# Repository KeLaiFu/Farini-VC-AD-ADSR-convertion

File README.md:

# Farini-VC-AD-ADSR-convertion
An attempt to convert a 3310 based VC ADSR from Kosmo format, to Eurorack

'3320' on the panel has been fixed!

Original Kosmo module by Dave can be found here:
https://github.com/DavesKosmoModules/Farini-VC-ADSR
Cheers Dave!

Current Status : initial build tested with spectacular results! My entire rack stopped producing audio apart from a high pitched noise coming from the PSU, so, I think I'll chalk this one up as a fail. My only 3310 chip is probably toasted now too, so I can't really continue to work on this, sadly.

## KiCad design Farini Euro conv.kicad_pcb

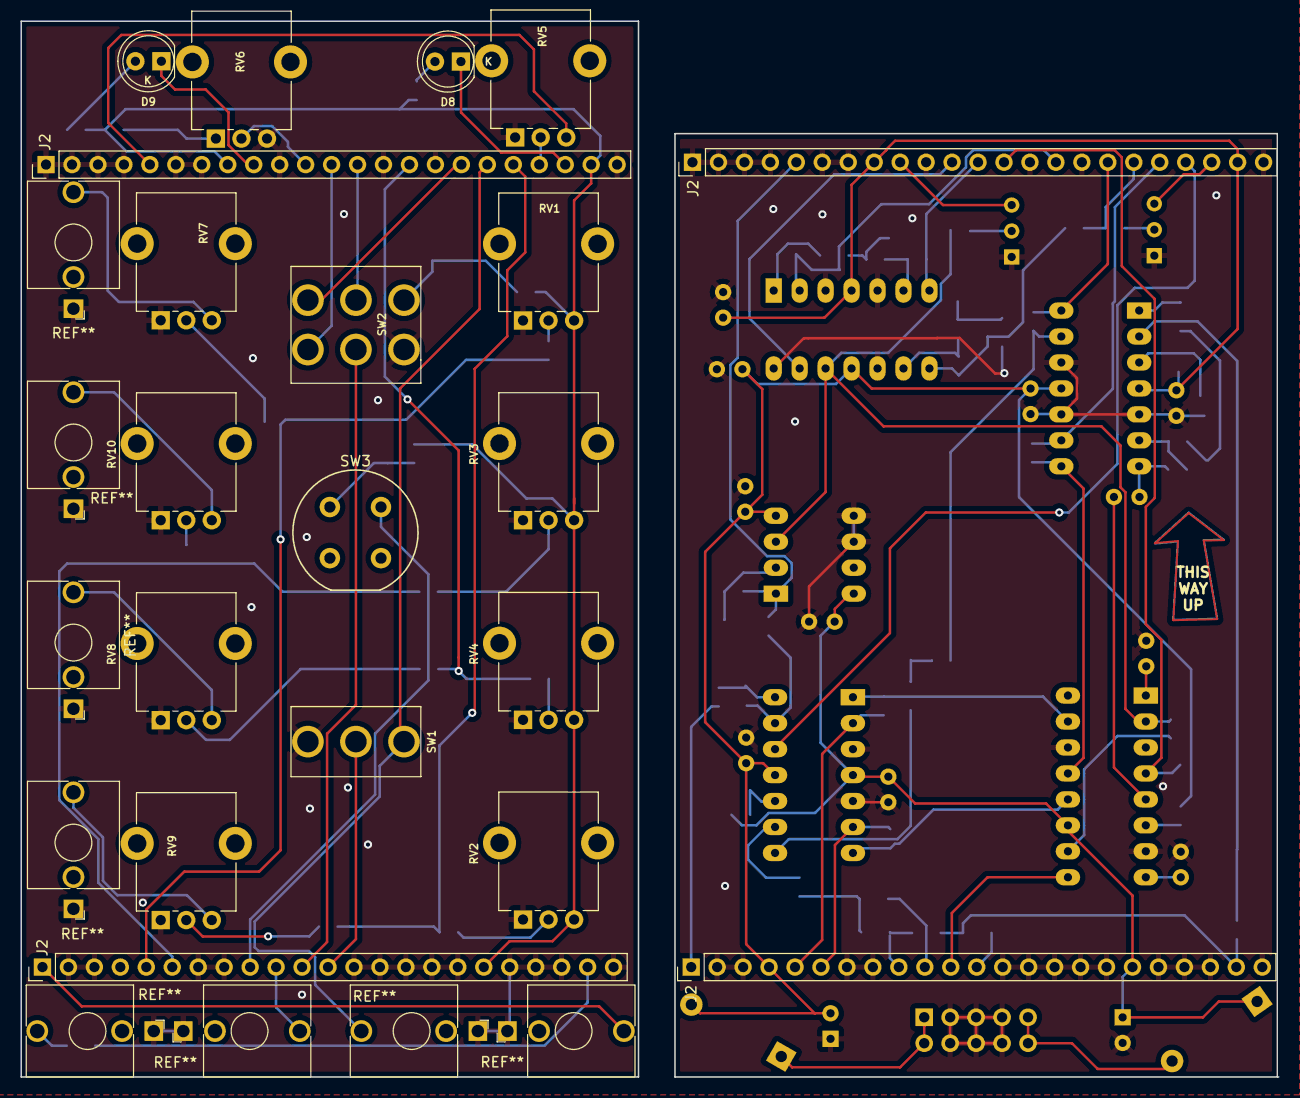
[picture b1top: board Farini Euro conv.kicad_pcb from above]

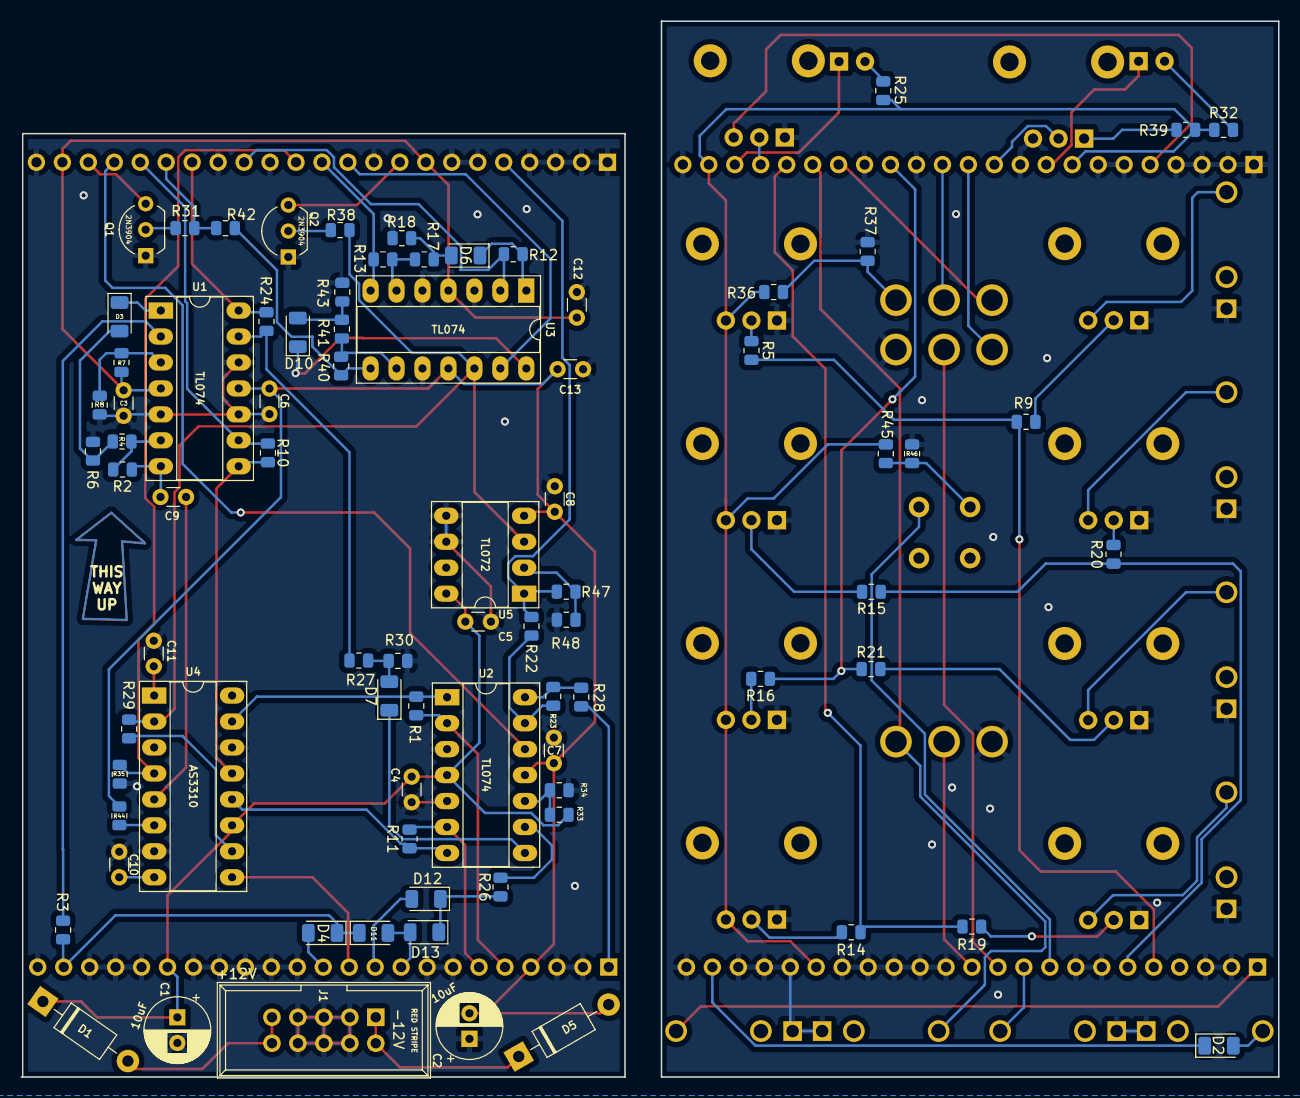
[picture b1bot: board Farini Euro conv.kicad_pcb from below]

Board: 2 copper layers, 123.1 x 103.3 mm, 99 parts (80 on the bottom side), 70 nets.

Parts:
C1, C2: 10uF; CP_Radial_D6.3mm_P2.50mm
C3, C4, C5, C6, C7, C8, C12, C13: 0.1uF; C_Disc_D3.0mm_W1.6mm_P2.50mm
C9: 0.001uF; C_Disc_D3.0mm_W1.6mm_P2.50mm
C10: 0.01uF; C_Disc_D3.0mm_W1.6mm_P2.50mm
C11: 0.03uF; C_Disc_D3.0mm_W1.6mm_P2.50mm
D1, D5: 1N5817; D_DO-41_SOD81_P10.16mm_Horizontal
D2, D3, D4, D6, D7, D10, D11, D12, D13: 1N4148; D_1206_3216Metric
D8, D9: LED; LED_D5.0mm
J1: Synth_power_2x5; Power_Header
J2, J2#2, J2#3, J2#4: Conn_01x10_Male; PinHeader_1x23_P2.54mm_Vertical
Q1, Q2: 2N3904; TO-92_Inline_Wide
R1, R10, R11: 6k2; R_0805_2012Metric
R2, R12, R24: 47k; R_0805_2012Metric
R3, R4, R5, R6, R8, R9, R13, R14, R15, R16, R17, R18, R19, R20, R21, R22, R23, R26, R27, R30, R31, R34, R37, R38, R39, R41, R43, R45, R46, R47, R48: 100k; R_0805_2012Metric
R7, R33: 200k; R_0805_2012Metric
R25, R32, R35: 10k; R_0805_2012Metric
R28, R42: 1k; R_0805_2012Metric
R29: 30k; R_0805_2012Metric
R36: link; R_0805_2012Metric
R40: 51k; R_0805_2012Metric
R44: 470; R_0805_2012Metric
RV1, RV2, RV3, RV4, RV5, RV7, RV8, RV9, RV10: 100k; Potentiometer_Alpha_RD901F-40-00D_Single_Vertical_CircularH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
RV6: 10k; Potentiometer_Alpha_RD901F-40-00D_Single_Vertical_CircularH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
SW1: SW_SPDT; SPDT-toggle-switch-1M-series
SW2: SW_DPDT_x2; DPDT-toggle-switch-1M-seriesx
SW3: SW_Push; Push_E-Switch_KS01Q01
U1, U2, U3: TL074; DIP-14_W7.62mm_Socket_LongPads
U4: AS3310; DIP-16_W7.62mm_Socket_LongPads
U5: TL072; DIP-8_W7.62mm_Socket_LongPads

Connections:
+12V: C1.1, C3.2, C4.2, C5.2, C12.2, D1.1, J2.18, J2#2.8, J2#2.22, J2#3.18, J2#4.8, J2#4.22, R7.2, R25.1, R32.1, R33.2, R36.2, R39.1, R45.1, RV1.3, RV2.3, RV3.3, RV4.3, U1.4, U2.4, U3.4, U4.11, U5.8
-12V: C2.2, C6.2, C7.2, C8.2, C13.2, D5.2, J2.4, J2#3.4, R44.2, U1.11, U2.11, U3.11, U5.4
/AttackControl: R1.1, U2.1, U4.15
/DecayControl: R11.1, U2.7, U4.12
/EocOut: J2#2.18, J2#4.18, R31.2, R42.1, SW1.3
/Gate: D12.2, J2.10, J2#3.10
/ManTrigger: D11.2, D13.2, J2.9, J2#3.9, SW3.2
/Out: J2.1, J2#3.1, R28.1
/ReleaseControl: R10.1, U1.8, U4.13
/SustainControl: J2.11, J2#3.11, SW2.2, U4.9
/VTrig: C9.2, R2.1, U1.7
/Vgate: J2#2.13, J2#4.13, R35.1, SW2.5, U4.4
/env: R29.1, R38.2, U3.12, U4.2, U5.3
GND: C1.2, C2.1, C3.1, C4.1, C5.1, C6.1, C7.1, C8.1, C10.1, C11.1, C12.1, C13.1, J1.3, J1.4, J1.5, J1.6, J1.7, J1.8, J2.2, J2.3, J2.7, J2.8, J2.13, J2.14, J2.15, J2.16, J2.17, J2.19, J2.20, J2.21, J2.23, J2#2.1, J2#2.2, J2#2.3, J2#2.4, J2#2.6, J2#2.7, J2#2.10, J2#2.14, J2#2.16, J2#2.23, J2#3.2, J2#3.3, J2#3.7, J2#3.8, J2#3.13, J2#3.14, J2#3.15, J2#3.16, J2#3.17, J2#3.19, J2#3.20, J2#3.21, J2#3.23, J2#4.1, J2#4.2, J2#4.3, J2#4.4, J2#4.6, J2#4.7, J2#4.10, J2#4.14, J2#4.16, J2#4.23, Q1.1, Q2.1, R6.1, R8.1, R18.1, R30.1, R34.1, R35.2, R37.1, R43.2, R46.2, R48.2, RV1.1, RV2.1, RV3.1, RV4.1, RV5.1, RV6.3, RV7.1, RV8.1, RV9.1, RV10.1, SW1.1, SW2.3, U1.5, U1.10, U1.12, U2.3, U2.5, U3.3, U3.5, U3.10, U4.7, U4.14, U5.5, U5.6
unnamed: C9.1, U4.5
unnamed: C10.2, U4.8
unnamed: C11.2, U4.1
unnamed: D1.2, J1.9, J1.10
unnamed: D3.1, U1.1
unnamed: D3.2, R4.2, R6.2
unnamed: D4.2, J2.12, J2#3.12, SW1.2
unnamed: D5.1, J1.1, J1.2
unnamed: D6.1, R12.1, U3.1
unnamed: D6.2, R17.2, R18.2
unnamed: D7.1, U2.8
unnamed: D7.2, R27.2, R30.2
unnamed: D8.1, J2#2.21, J2#4.21, Q1.3
unnamed: D8.2, R25.2
unnamed: D9.1, J2#2.9, J2#4.9, Q2.3
unnamed: D9.2, R32.2
unnamed: D10.1, U3.14
unnamed: D10.2, R41.2, R43.1
unnamed: D2.1, D4.1, D11.1, J2.22, J2#3.22, R3.2
unnamed: D12.1, D13.1, R26.2
unnamed: Q1.2, R31.1
unnamed: Q2.2, R38.1
unnamed: J2.5, J2#3.5, R1.2, R5.1, R9.1, U2.2
unnamed: R2.2, R4.1, U1.6
unnamed: R3.1, U1.2
unnamed: R5.2, RV1.2
unnamed: R7.1, R8.2, U1.3
unnamed: R9.2, RV7.2
unnamed: J2#2.19, J2#4.19, R10.2, R14.1, R19.1, U1.9
unnamed: J2.6, J2#3.6, R11.2, R15.1, R20.1, U2.6
unnamed: J2#2.15, J2#4.15, R12.2, R16.1, R21.1, U3.2
unnamed: J2#2.12, J2#4.12, R13.1, SW2.1, U3.7
unnamed: R13.2, R17.1, U3.6
unnamed: R14.2, RV2.2
unnamed: R15.2, RV3.2
unnamed: R16.2, RV4.2
unnamed: R19.2, RV9.2
unnamed: R20.2, RV10.2
unnamed: R21.2, RV8.2
unnamed: R22.1, R23.2, U2.13
unnamed: J2#2.5, J2#4.5, R22.2, R47.2, RV5.3, U5.1
unnamed: R23.1, R28.2, U2.14
unnamed: J2#2.17, J2#4.17, R24.1, SW2.4, U1.14
unnamed: R24.2, R27.1, U1.13
unnamed: R26.1, U2.9
unnamed: R29.2, U4.10
unnamed: R33.1, R34.2, U2.10
unnamed: R36.1, R37.2, SW2.6
unnamed: R39.2, RV6.1
unnamed: R40.1, R42.2, U3.8
unnamed: R40.2, R41.1, U3.9
unnamed: R44.1, U4.6
unnamed: R45.2, R46.1, SW3.1
unnamed: R47.1, R48.1, U5.2
unnamed: J2#2.20, J2#4.20, RV5.2, U2.12
unnamed: J2#2.11, J2#4.11, RV6.2, U3.13

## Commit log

2021-11-22 Add files via upload
    11.22.2021 reformatted the layout to suit vertical main pots
